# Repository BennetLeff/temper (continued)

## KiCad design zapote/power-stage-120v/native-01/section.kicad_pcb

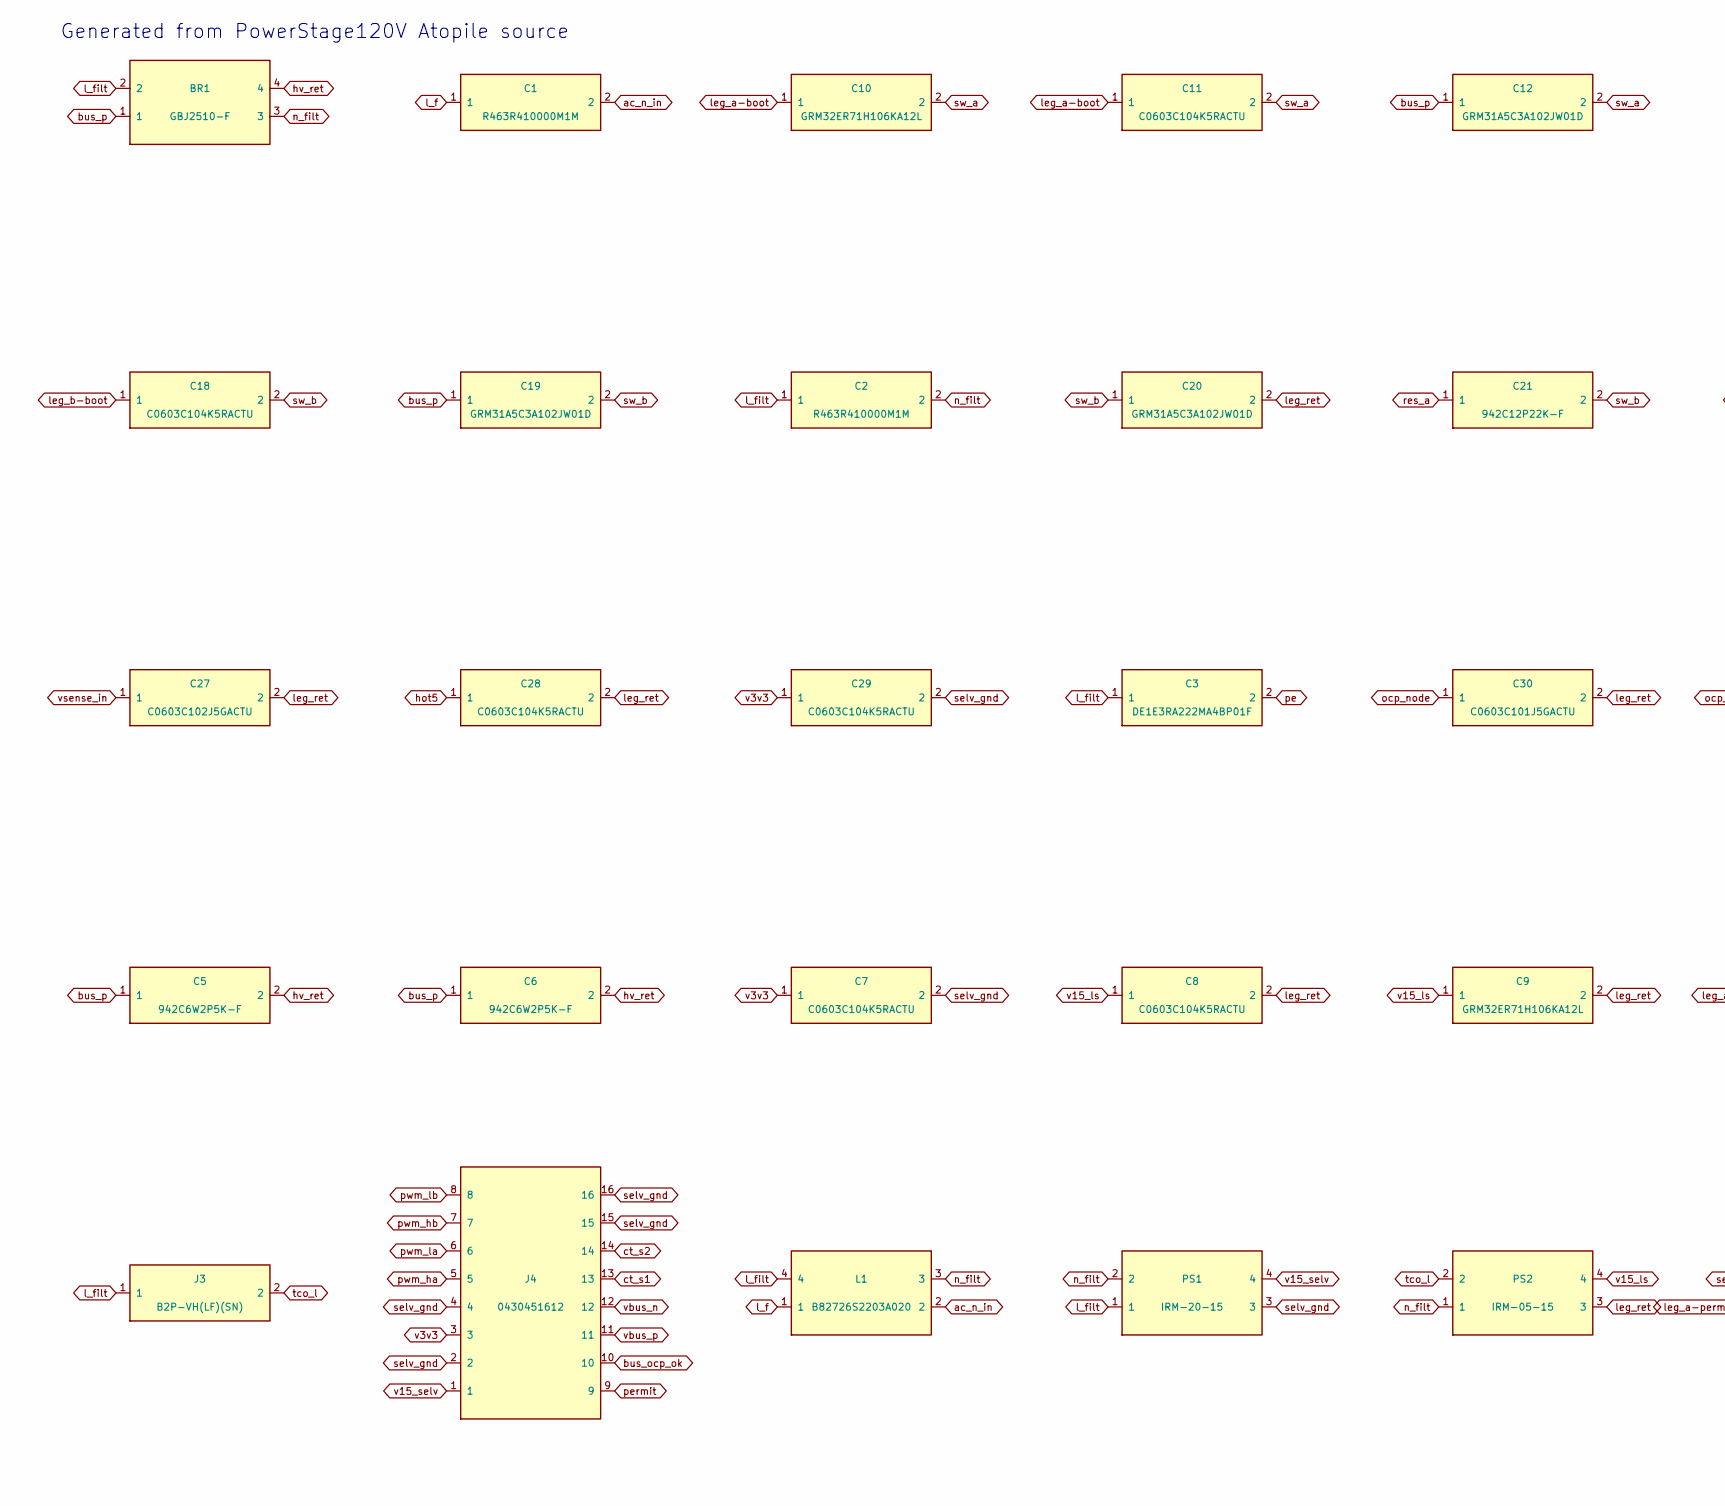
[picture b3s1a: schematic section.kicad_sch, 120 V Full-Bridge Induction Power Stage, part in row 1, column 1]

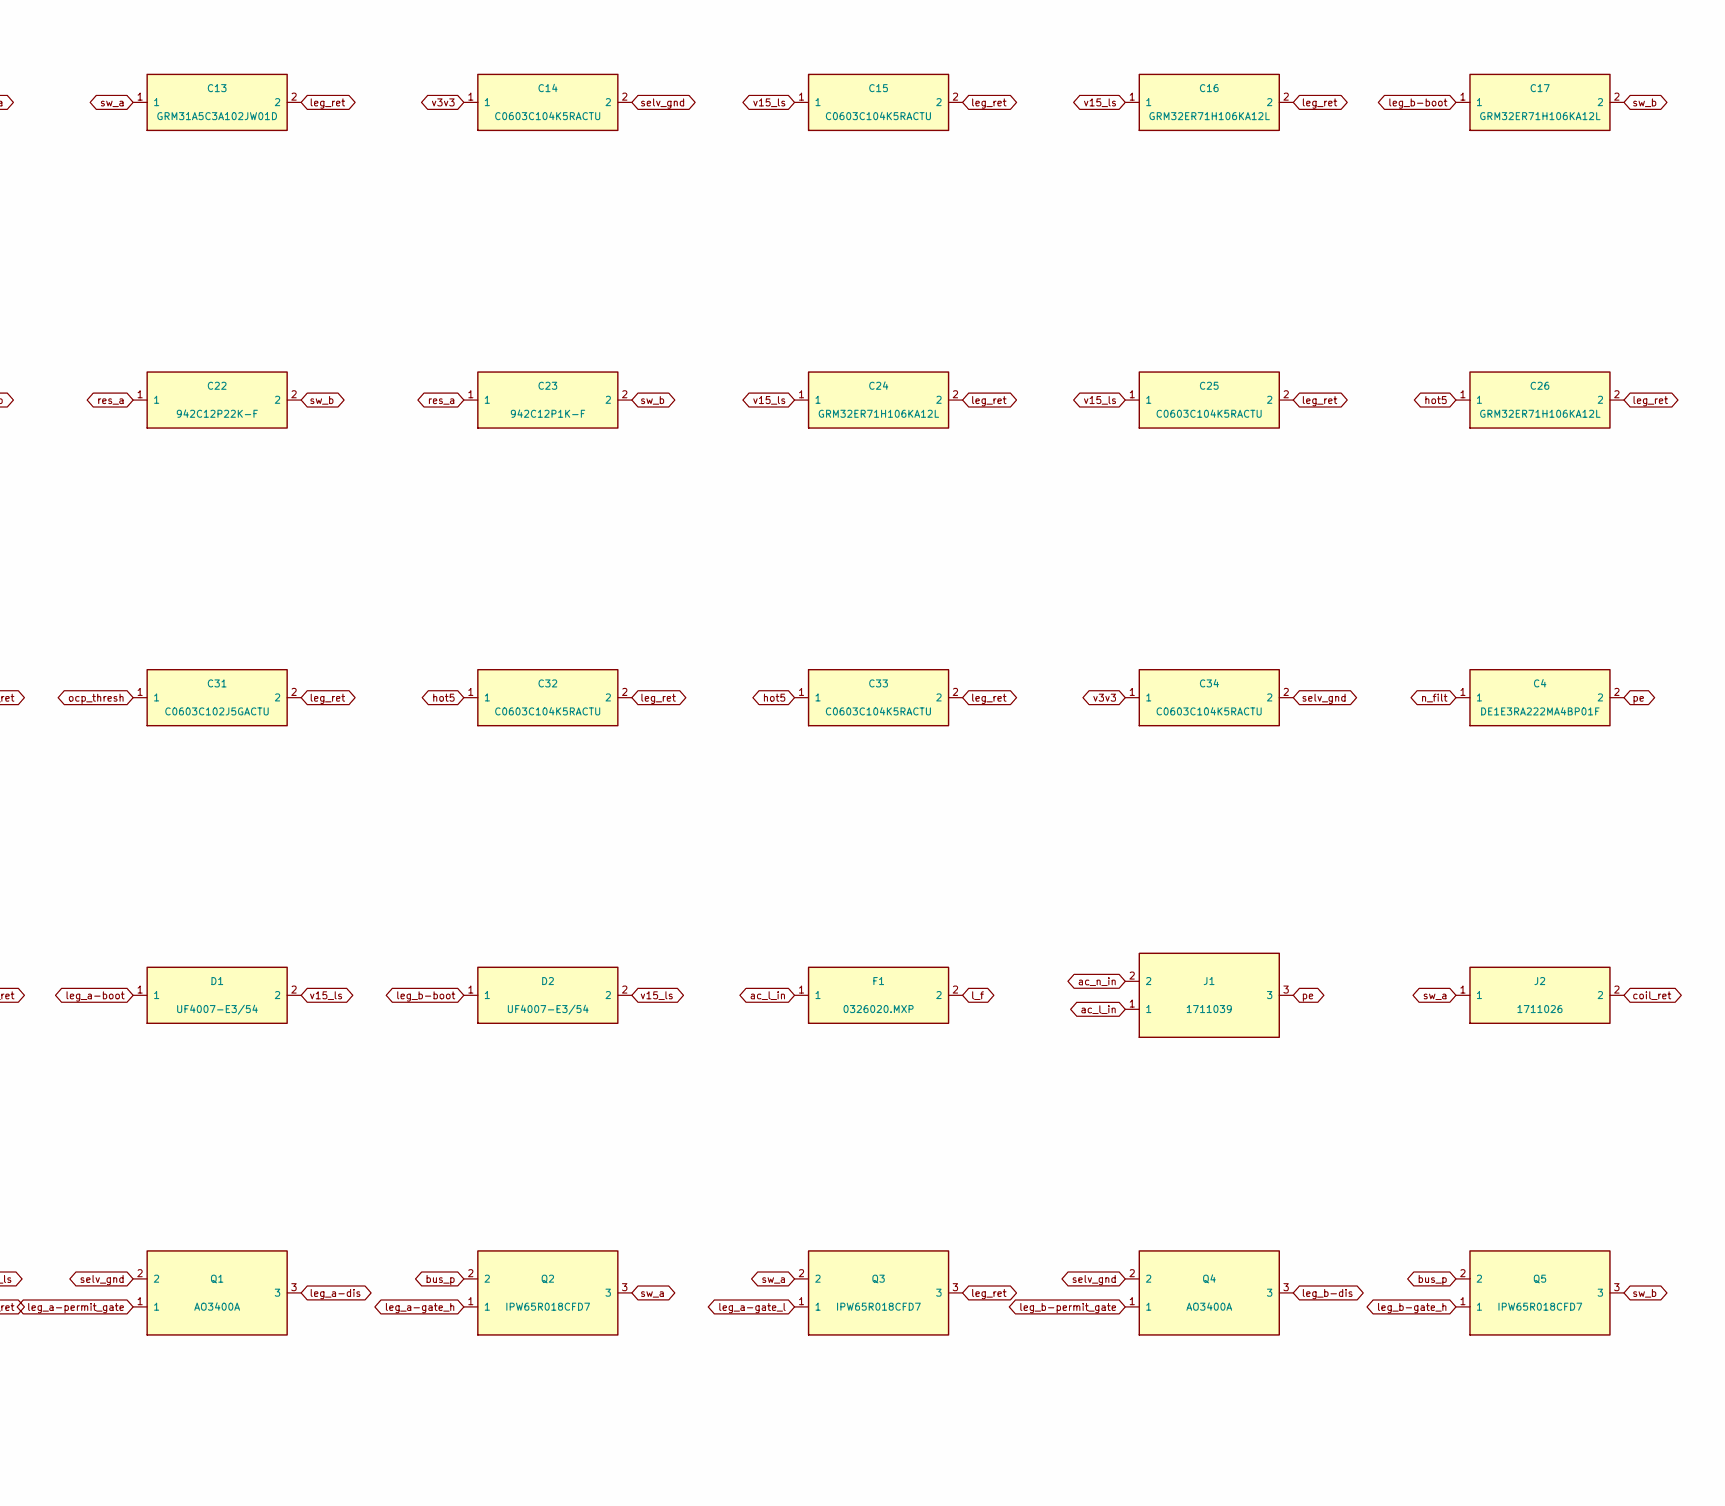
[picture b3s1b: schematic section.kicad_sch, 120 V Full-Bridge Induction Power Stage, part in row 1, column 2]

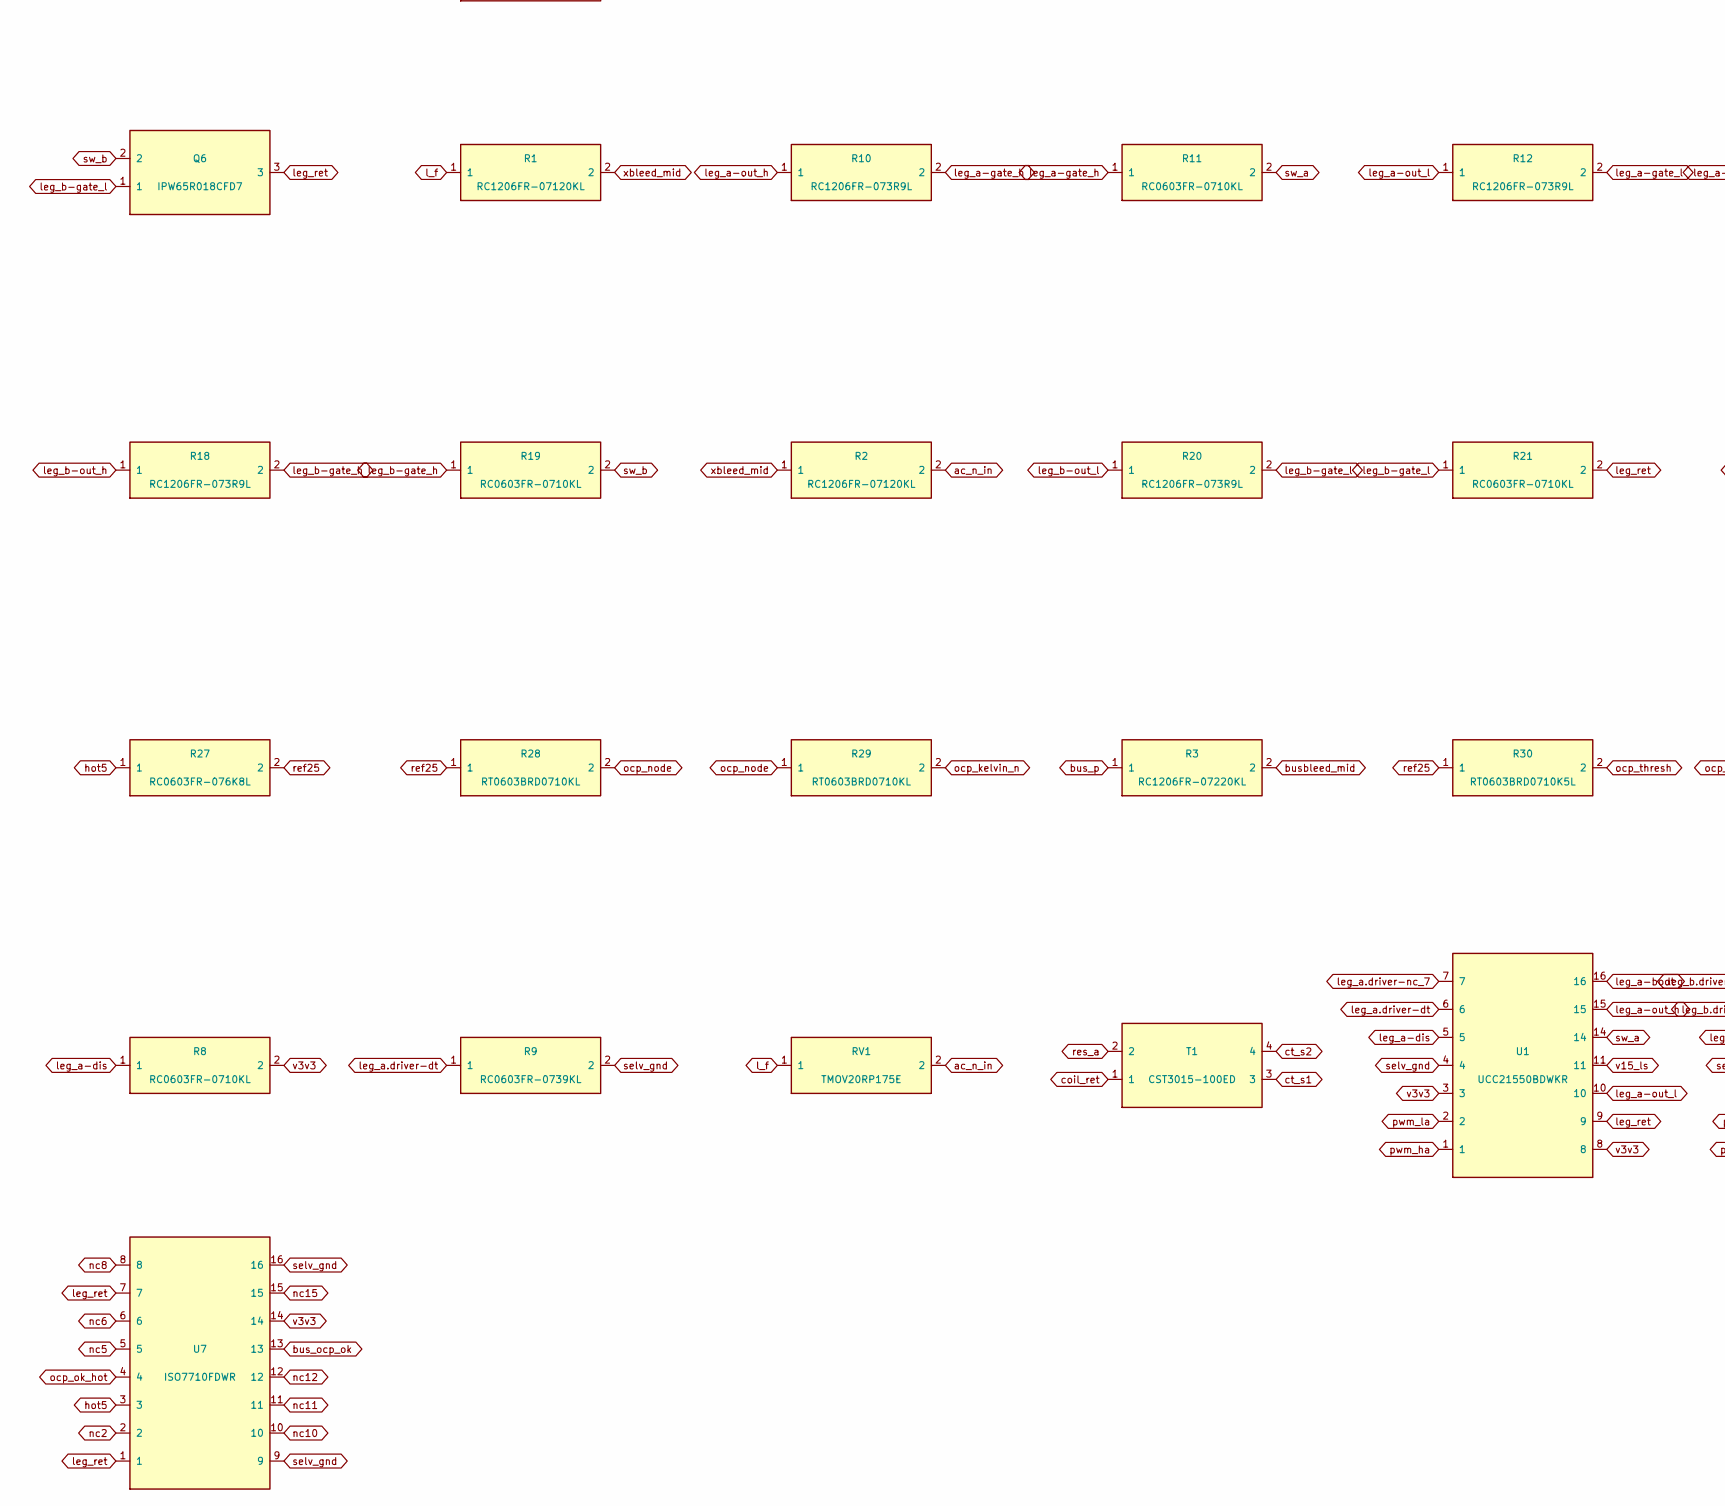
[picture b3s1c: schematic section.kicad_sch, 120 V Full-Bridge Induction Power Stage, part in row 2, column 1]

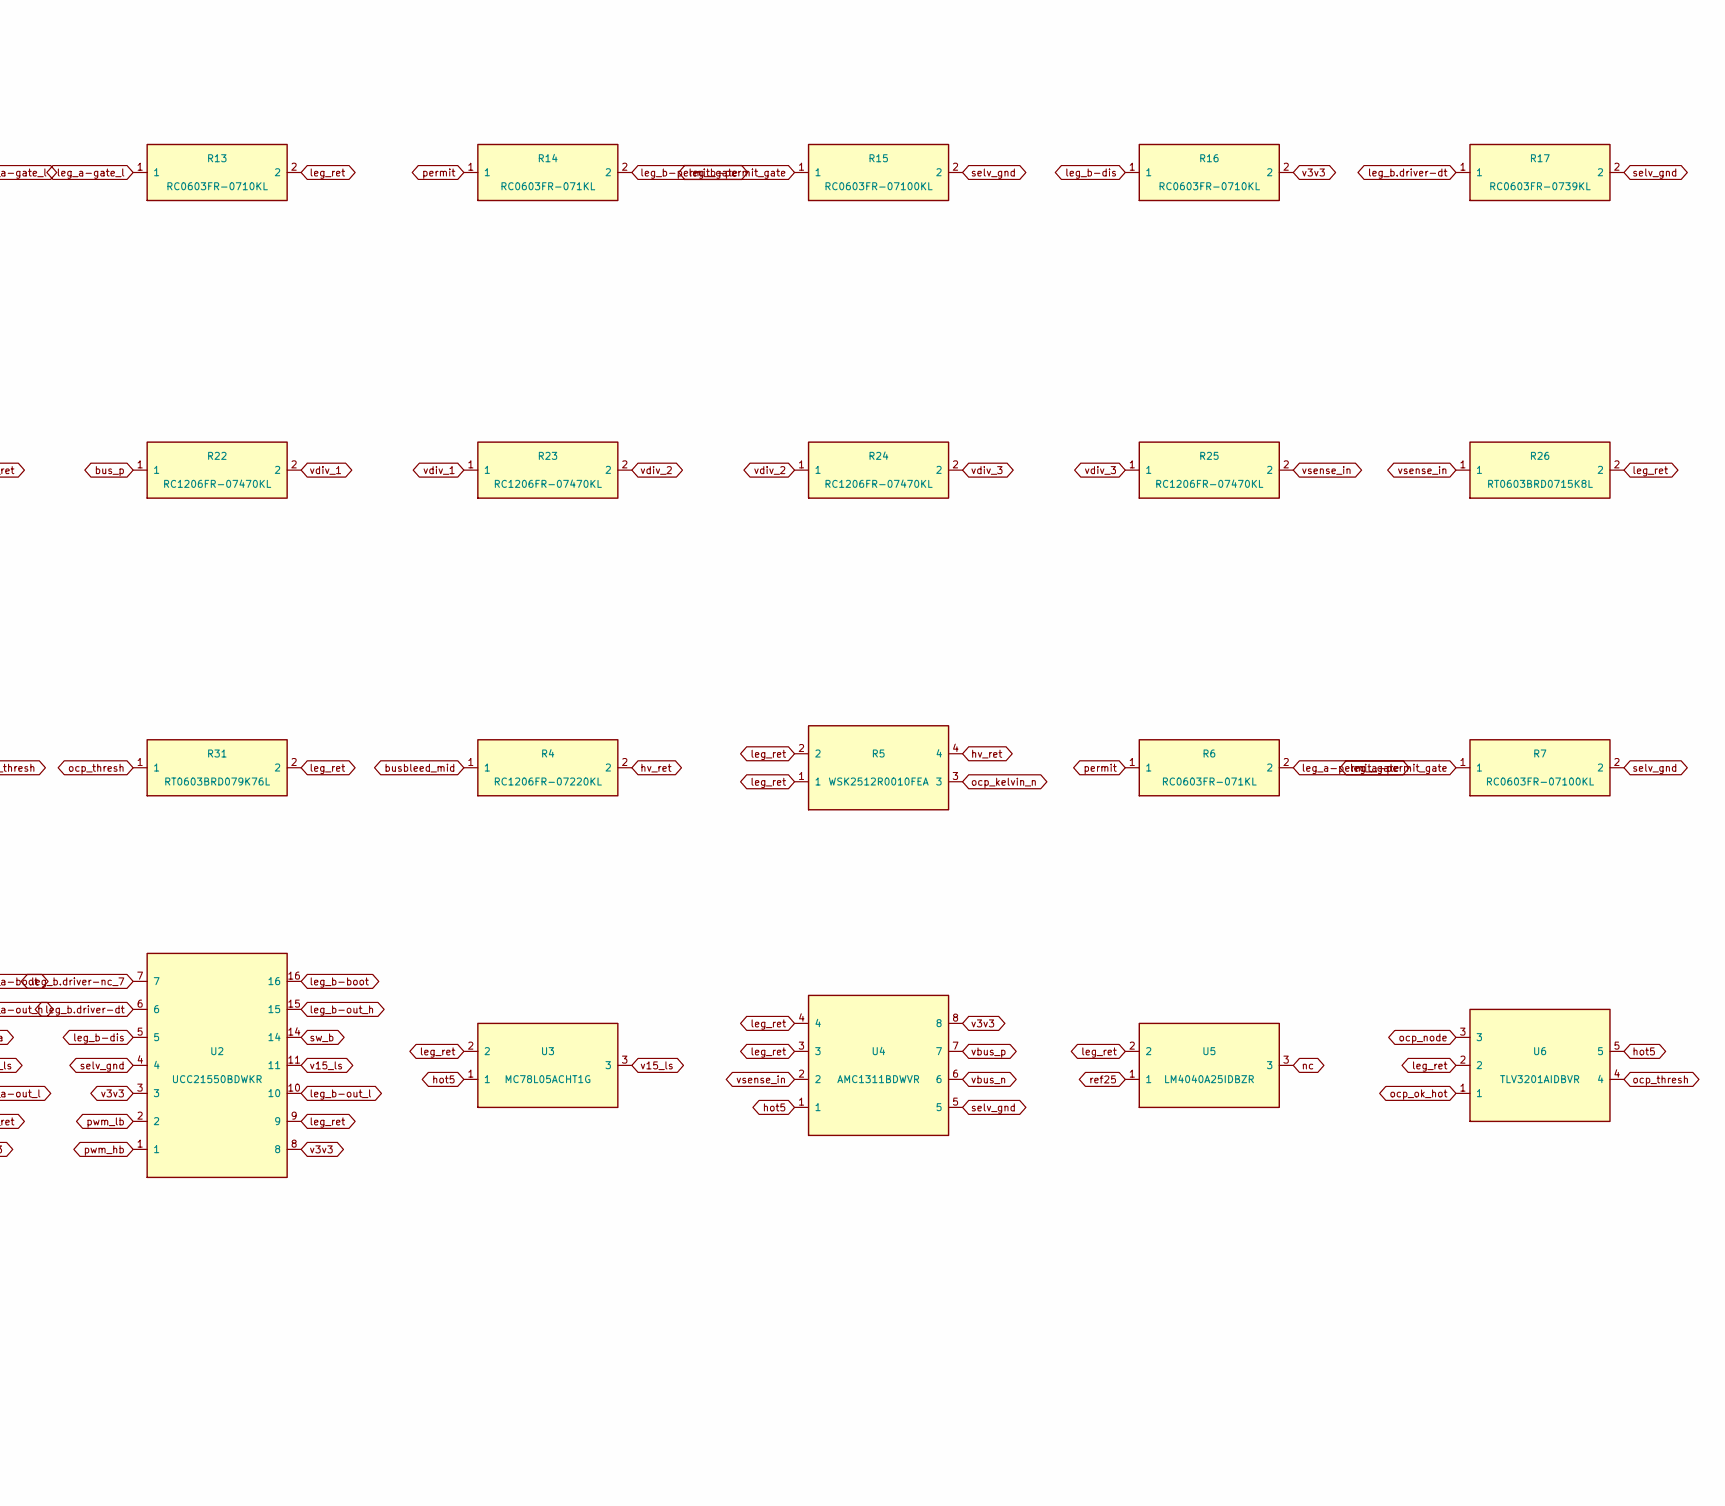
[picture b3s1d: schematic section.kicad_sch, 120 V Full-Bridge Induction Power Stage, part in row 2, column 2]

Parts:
BR1: GBJ2510-F; Diode_Bridge_GBJ2510
C1, C2: R463R410000M1M; C_Rect_L26.5mm_W10.5mm_P22.50mm_MKS4
C3, C4: DE1E3RA222MA4BP01F; C_Disc_D10.5mm_W5.0mm_P10.00mm
C5, C6: 942C6W2P5K-F; CDE_942C_D32.0_L54.0_Axial_ReviewOnly
C7, C8, C11, C14, C15, C18, C25, C28, C29, C32, C33, C34: C0603C104K5RACTU; C_0603_1608Metric
C9, C10, C16, C17, C24, C26: GRM32ER71H106KA12L; C_1210_3225Metric
C12, C13, C19, C20: GRM31A5C3A102JW01D; C_1206_3216Metric
C21, C22: 942C12P22K-F; CDE_942C_D26.5_L34.0_Axial_ReviewOnly
C23: 942C12P1K-F; CDE_942C_D19.0_L34.0_Axial_ReviewOnly
C27, C31: C0603C102J5GACTU; C_0603_1608Metric
C30: C0603C101J5GACTU; C_0603_1608Metric
D1, D2: UF4007-E3/54; D_DO-41_SOD81_P10.16mm_Horizontal
F1: 0326020.MXP; Fuseholder_Clip-6.3x32mm_Littelfuse_102071_Inline_P34.70x7.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
J1: 1711039; TerminalBlock_Phoenix_MKDS-3-3-5.08_1x03_P5.08mm_Horizontal
J2: 1711026; TerminalBlock_Phoenix_MKDS-3-2-5.08_1x02_P5.08mm_Horizontal
J3: B2P-VH(LF)(SN); JST_VH_B2P-VH_1x02_P3.96mm_Vertical
J4: 0430451612; Molex_Micro-Fit_3.0_43045-1612_2x08_P3.00mm_Vertical
L1: B82726S2203A020; B82726S2_ReviewOnly
PS1: IRM-20-15; Converter_ACDC_MeanWell_IRM-20-xx_THT
PS2: IRM-05-15; Converter_ACDC_MeanWell_IRM-05-xx_THT
Q1, Q4: AO3400A; SOT-23
Q2, Q3, Q5, Q6: IPW65R018CFD7; TO-247-3_Vertical
R1, R2: RC1206FR-07120KL; R_1206_3216Metric
R3, R4: RC1206FR-07220KL; R_1206_3216Metric
R5: WSK2512R0010FEA; R_Shunt_Vishay_WSK2512_6332Metric_T1.19mm
R6, R14: RC0603FR-071KL; R_0603_1608Metric
R7, R15: RC0603FR-07100KL; R_0603_1608Metric
R8, R11, R13, R16, R19, R21: RC0603FR-0710KL; R_0603_1608Metric
R9, R17: RC0603FR-0739KL; R_0603_1608Metric
R10, R12, R18, R20: RC1206FR-073R9L; R_1206_3216Metric
R22, R23, R24, R25: RC1206FR-07470KL; R_1206_3216Metric
R26: RT0603BRD0715K8L; R_0603_1608Metric
R27: RC0603FR-076K8L; R_0603_1608Metric
R28, R29: RT0603BRD0710KL; R_0603_1608Metric
R30: RT0603BRD0710K5L; R_0603_1608Metric
R31: RT0603BRD079K76L; R_0603_1608Metric
RV1: TMOV20RP175E; TMOV20RP_ReviewOnly
T1: CST3015-100ED; CST3015
U1, U2: UCC21550BDWKR; SOIC16W_Isolated
U3: MC78L05ACHT1G; SOT-89-3
U4: AMC1311BDWVR; SOIC-8_7.5x5.85mm_P1.27mm
U5: LM4040A25IDBZR; SOT-23
U6: TLV3201AIDBVR; SOT-23-5
U7: ISO7710FDWR; SOIC-16W_7.5x10.3mm_P1.27mm

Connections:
ac_l_in: F1.1, J1.1
ac_n_in: C1.2, J1.2, L1.2, R2.2, RV1.2
bus_ocp_ok: J4.10, U7.13
bus_p: BR1.1, C5.1, C6.1, C12.1, C19.1, Q2.2, Q5.2, R3.1, R22.1
busbleed_mid: R3.2, R4.1
coil_ret: J2.2, T1.1
ct_s1: J4.13, T1.3
ct_s2: J4.14, T1.4
hot5: C26.1, C28.1, C32.1, C33.1, R27.1, U3.1, U4.1, U6.5, U7.3
hv_ret: BR1.4, C5.2, C6.2, R4.2, R5.4
l_f: C1.1, F1.2, L1.1, R1.1, RV1.1
l_filt: BR1.2, C2.1, C3.1, J3.1, L1.4, PS1.1
leg_a-boot: C10.1, C11.1, D1.1, U1.16
leg_a-dis: Q1.3, R8.1, U1.5
leg_a-gate_h: Q2.1, R10.2, R11.1
leg_a-gate_l: Q3.1, R12.2, R13.1
leg_a-out_h: R10.1, U1.15
leg_a-out_l: R12.1, U1.10
leg_a-permit_gate: Q1.1, R6.2, R7.1
leg_a.driver-dt: R9.1, U1.6
leg_a.driver-nc_7: U1.7
leg_b-boot: C17.1, C18.1, D2.1, U2.16
leg_b-dis: Q4.3, R16.1, U2.5
leg_b-gate_h: Q5.1, R18.2, R19.1
leg_b-gate_l: Q6.1, R20.2, R21.1
leg_b-out_h: R18.1, U2.15
leg_b-out_l: R20.1, U2.10
leg_b-permit_gate: Q4.1, R14.2, R15.1
leg_b.driver-dt: R17.1, U2.6
leg_b.driver-nc_7: U2.7
leg_ret: C8.2, C9.2, C13.2, C15.2, C16.2, C20.2, C24.2, C25.2, C26.2, C27.2, C28.2, C30.2, C31.2, C32.2, C33.2, PS2.3, Q3.3, Q6.3, R5.1, R5.2, R13.2, R21.2, R26.2, R31.2, U1.9, U2.9, U3.2, U4.3, U4.4, U5.2, U6.2, U7.1, U7.7
n_filt: BR1.3, C2.2, C4.1, L1.3, PS1.2, PS2.1
nc: U5.3
nc2: U7.2
nc5: U7.5
nc6: U7.6
nc8: U7.8
nc10: U7.10
nc11: U7.11
nc12: U7.12
nc15: U7.15
ocp_kelvin_n: R5.3, R29.2
ocp_node: C30.1, R28.2, R29.1, U6.3
ocp_ok_hot: U6.1, U7.4
ocp_thresh: C31.1, R30.2, R31.1, U6.4
pe: C3.2, C4.2, J1.3
permit: J4.9, R6.1, R14.1
pwm_ha: J4.5, U1.1
pwm_hb: J4.7, U2.1
pwm_la: J4.6, U1.2
pwm_lb: J4.8, U2.2
ref25: R27.2, R28.1, R30.1, U5.1
res_a: C21.1, C22.1, C23.1, T1.2
selv_gnd: C7.2, C14.2, C29.2, C34.2, J4.2, J4.4, J4.15, J4.16, PS1.3, Q1.2, Q4.2, R7.2, R9.2, R15.2, R17.2, U1.4, U2.4, U4.5, U7.9, U7.16
sw_a: C10.2, C11.2, C12.2, C13.1, J2.1, Q2.3, Q3.2, R11.2, U1.14
sw_b: C17.2, C18.2, C19.2, C20.1, C21.2, C22.2, C23.2, Q5.3, Q6.2, R19.2, U2.14
tco_l: J3.2, PS2.2
v3v3: C7.1, C14.1, C29.1, C34.1, J4.3, R8.2, R16.2, U1.3, U1.8, U2.3, U2.8, U4.8, U7.14
v15_ls: C8.1, C9.1, C15.1, C16.1, C24.1, C25.1, D1.2, D2.2, PS2.4, U1.11, U2.11, U3.3
v15_selv: J4.1, PS1.4
vbus_n: J4.12, U4.6
vbus_p: J4.11, U4.7
vdiv_1: R22.2, R23.1
vdiv_2: R23.2, R24.1
vdiv_3: R24.2, R25.1
vsense_in: C27.1, R25.2, R26.1, U4.2
xbleed_mid: R1.2, R2.1

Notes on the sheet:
Generated from PowerStage120V Atopile source

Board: 6 copper layers, 91 parts (0 on the bottom side), 56 nets, no tracks yet.
